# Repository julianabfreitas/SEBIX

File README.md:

# SEBIX
Projeto desenvolvido pela Diretoria 2020 da ADA - Projetos em Engenharia de Computação.
### Membros:
- Érika Cardoso
- Gabriela Vidal
- Juliana Freitas
- Patrick Feitosa

## Descrição do Projeto
Replicação do jogo "Dinosaur Game" feito pelo Google em Arduino. 

## Esquemático
Abaixo encontra-se o esquemático do projeto, utilizando um Arduino Nano.

## Descrição do jogo
Foram utilizados três push buttons que tem as funções de fazer o dinossauro subir na tela, descer na tela e resetar o jogo.
Também são emitidos alertas sonoros pelo buzzer, o potenciômetro foi utilizado para regular o volume do som emitido.

## Componentes utilizados
Para o projeto, utilizamos somente os componentes listados abaixo:
- 1 Arduino Nano
  - Eagle: componente baixado da internet, juntamente com seu modelo 3D
- 1 Leitor LCD 16x2
  - Eagle: componente baixado da internet, juntamente com seu modelo 3D
- 3 Botões
  - Eagle: B3F-40XX (Version 2)
- 1 Potenciômetro
  -  Eagle: 3RP/1610N (Version 2)
- 1 Buzzer
  - Eagle: F/QMB (Version 2)
- 4 Resistores de 10kΩ
  - Eagle: R-US_0207/10 (R-US_) (Version 1)
  
## PCB
Cada um dos integrantes do grupo desenvolveu uma PCB no software Eagle com o objetivo de que todos obtivessem conhecimentos nessa tecnologia. Aqui estão os modelos criados:

## Caixa
A caixa foi desenvolvida no software Fusion360, abaixo estão os modelos desenvolvidos.

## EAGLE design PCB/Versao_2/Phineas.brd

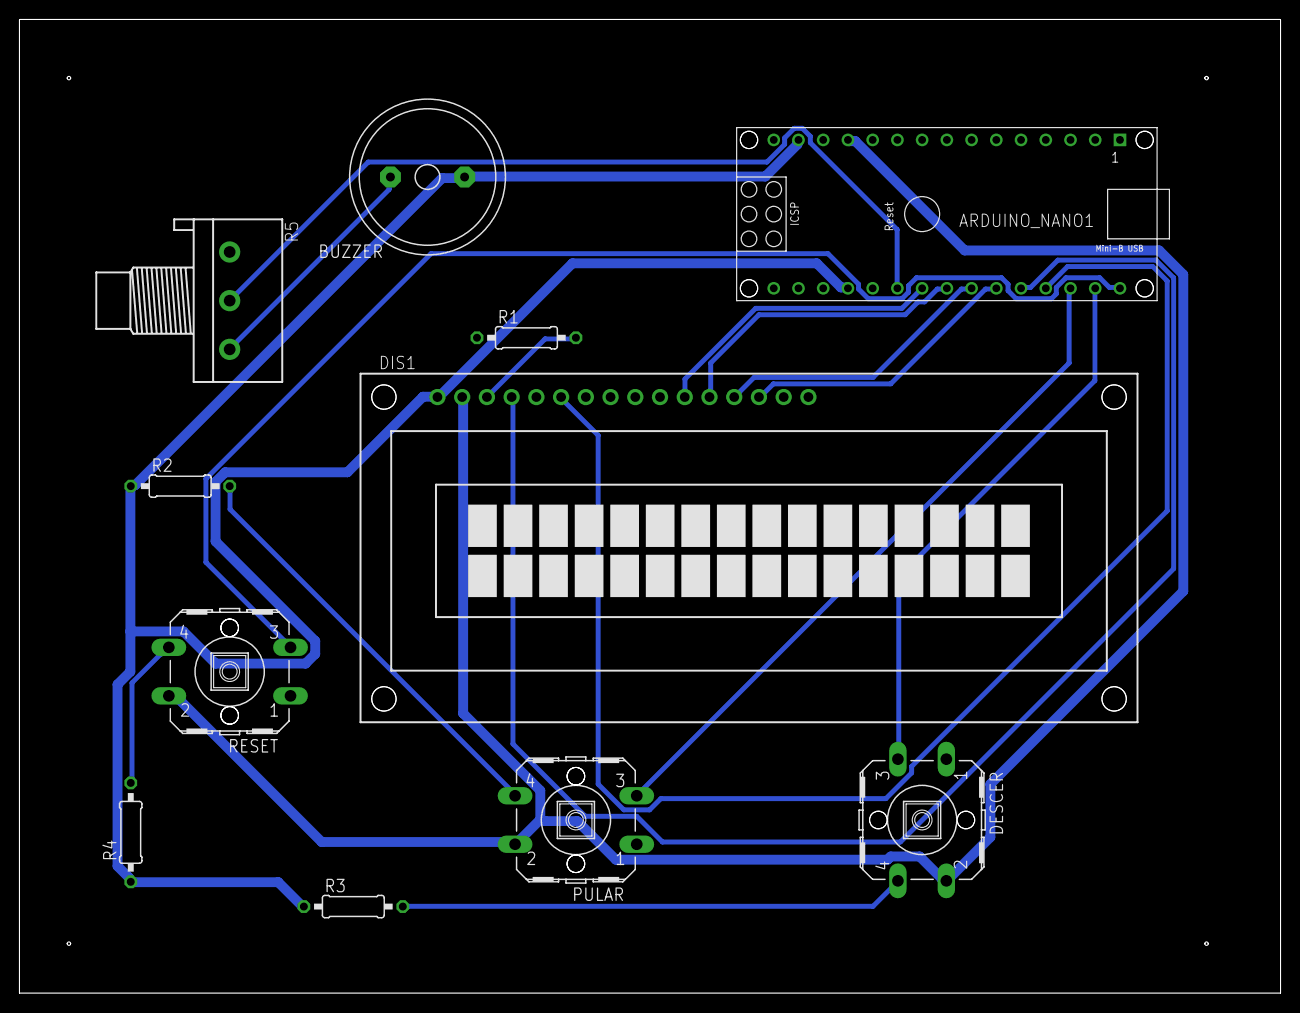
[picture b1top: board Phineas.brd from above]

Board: 2 copper layers, 129.5 x 100.0 mm, 11 parts (0 on the bottom side), 17 nets.

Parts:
ARDUINO_NANO1: ARDUINO_NANO
BUZZER: F/QMB
DESCER: B3F-40XX
DIS1: TUXGR_16X2_R2
PULAR: B3F-40XX
R1, R2, R3, R4: 0207/10
R5: 3RP/1610N
RESET: B3F-40XX

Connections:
GND: ARDUINO_NANO1.14, ARDUINO_NANO1.19, BUZZER.-, DIS1.1, R2.1, R3.1, R4.1
unnamed: DIS1.3, R1.2
unnamed: PULAR.4, R2.2
unnamed: DESCER.4, R3.2
unnamed: ARDUINO_NANO1.26, DIS1.4
unnamed: ARDUINO_NANO1.30, RESET.3
unnamed: ARDUINO_NANO1.29, DESCER.3
unnamed: ARDUINO_NANO1.28, PULAR.3
unnamed: ARDUINO_NANO1.27, DIS1.6
unnamed: BUZZER.+, R5.3
unnamed: ARDUINO_NANO1.25, DIS1.14
unnamed: ARDUINO_NANO1.24, DIS1.13
unnamed: ARDUINO_NANO1.23, DIS1.12
unnamed: ARDUINO_NANO1.22, DIS1.11
unnamed: R4.2, RESET.4
unnamed: ARDUINO_NANO1.21, R5.2
VCC: ARDUINO_NANO1.12, DESCER.2, DIS1.2, PULAR.2, RESET.2

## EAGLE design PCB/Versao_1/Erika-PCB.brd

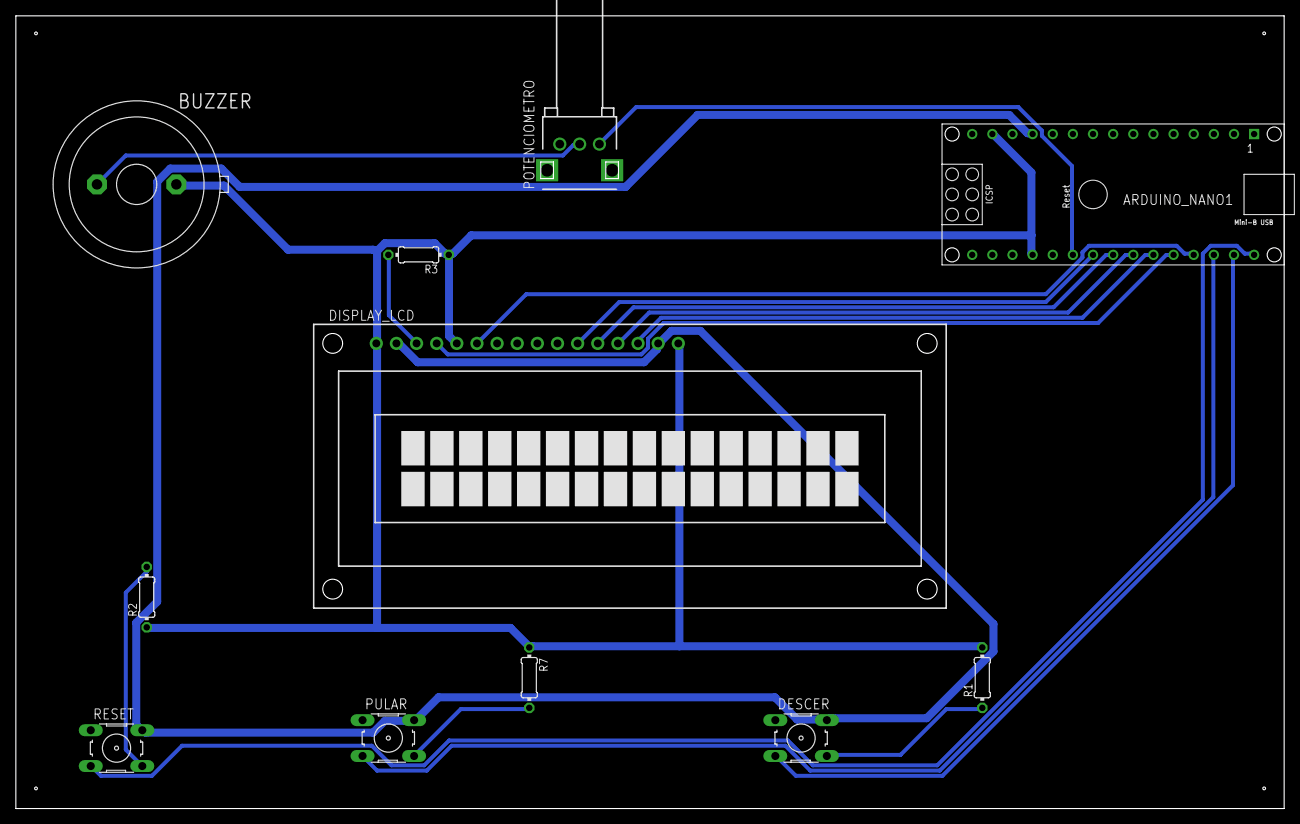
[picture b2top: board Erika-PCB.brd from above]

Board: 2 copper layers, 160.0 x 100.0 mm, 11 parts (0 on the bottom side), 17 nets.

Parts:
ARDUINO_NANO1: ARDUINO_NANO
BUZZER: F/EE21P
DESCER: B3F-10XX
DISPLAY_LCD: TUXGR_16X2_R2
POTENCIOMETRO: EVUE2A; EVUE
PULAR: B3F-10XX
R1, R2, R3, R7: 0204/7
RESET: B3F-10XX

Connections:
GND: ARDUINO_NANO1.14, ARDUINO_NANO1.19, BUZZER.2, DISPLAY_LCD.1, DISPLAY_LCD.5, DISPLAY_LCD.16, R1.2, R2.1, R3.1, R7.1
unnamed: ARDUINO_NANO1.22, DISPLAY_LCD.11
unnamed: DESCER.4, R1.1
unnamed: ARDUINO_NANO1.28, PULAR.3
unnamed: ARDUINO_NANO1.29, DESCER.3
unnamed: ARDUINO_NANO1.30, RESET.3
unnamed: BUZZER.1, POTENCIOMETRO.2
unnamed: ARDUINO_NANO1.23, DISPLAY_LCD.12
unnamed: R2.2, RESET.4
unnamed: PULAR.4, R7.2
unnamed: DISPLAY_LCD.3, R3.2
unnamed: ARDUINO_NANO1.24, DISPLAY_LCD.13
unnamed: ARDUINO_NANO1.25, DISPLAY_LCD.14
unnamed: ARDUINO_NANO1.26, DISPLAY_LCD.4
unnamed: ARDUINO_NANO1.27, DISPLAY_LCD.6
unnamed: ARDUINO_NANO1.21, POTENCIOMETRO.1
VCC: ARDUINO_NANO1.12, DESCER.2, DISPLAY_LCD.2, DISPLAY_LCD.15, PULAR.2, RESET.2

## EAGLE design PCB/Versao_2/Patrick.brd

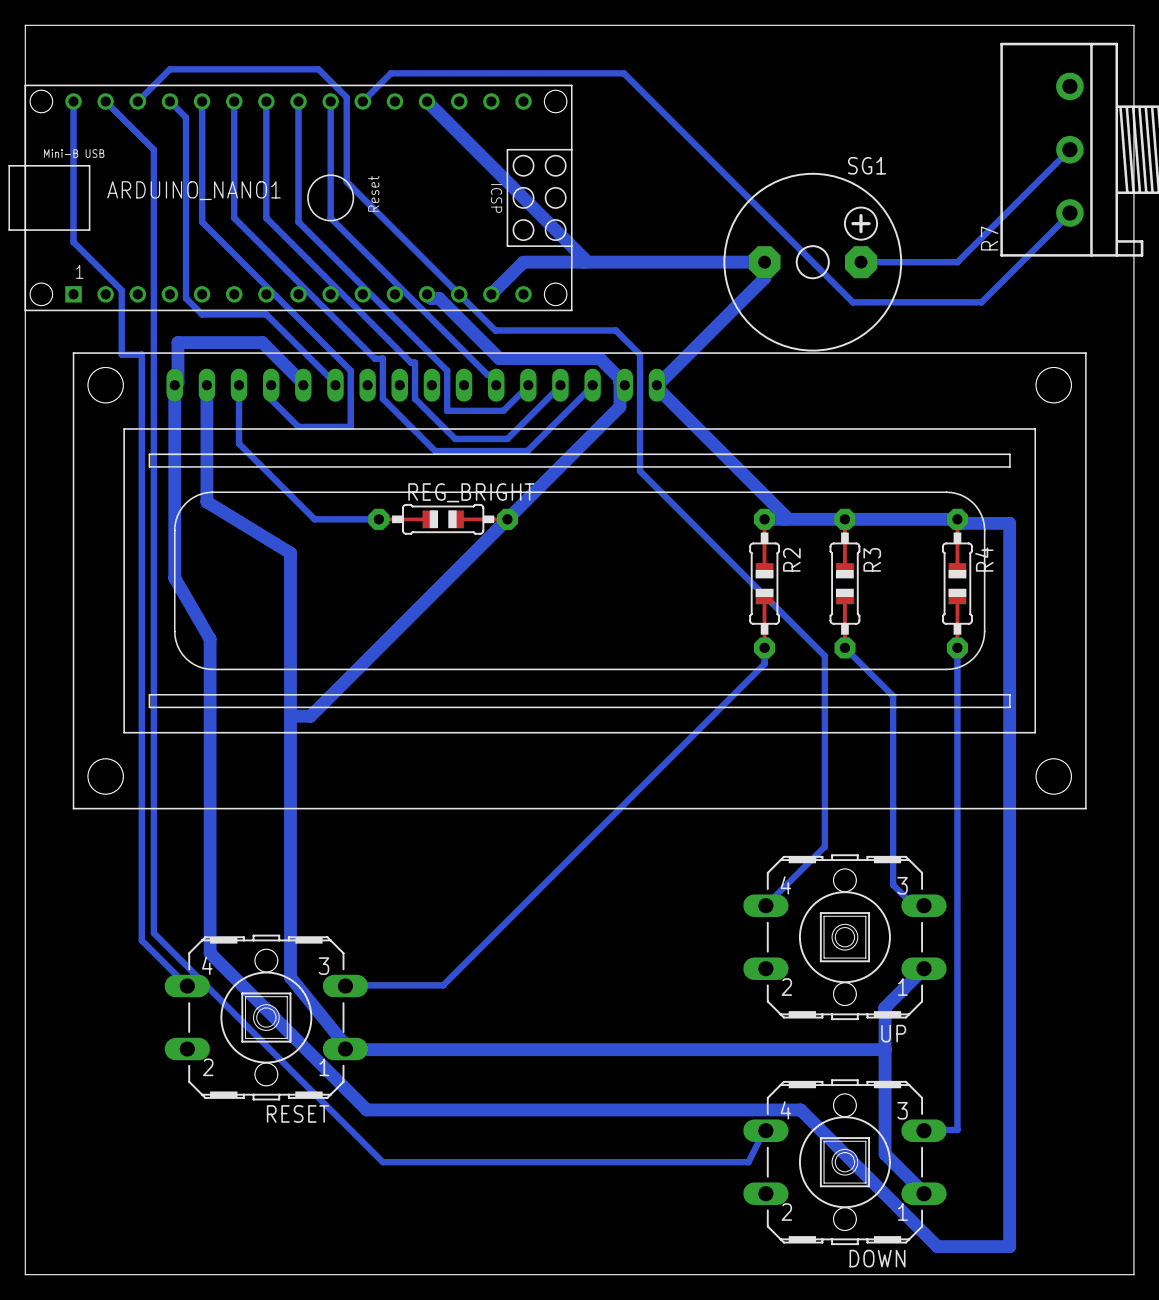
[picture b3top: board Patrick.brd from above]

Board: 2 copper layers, 87.6 x 98.7 mm, 11 parts (0 on the bottom side), 17 nets.

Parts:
ARDUINO_NANO1: ARDUINO_NANO
DOWN: B3F-40XX
R2, R3, R4: 0805-THM
R7: 3RP/1610N
REG_BRIGHT: 0805-THM
RESET: B3F-40XX
SG1: F/CM12P
UP: B3F-40XX
X1: HD44780LCD-1602; LCD1602

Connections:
GND: ARDUINO_NANO1.14, ARDUINO_NANO1.19, R2.1, R3.1, R4.1, SG1.-, X1.1, X1.5, X1.16
unnamed: REG_BRIGHT.1, X1.3
unnamed: ARDUINO_NANO1.28, UP.4
unnamed: ARDUINO_NANO1.29, DOWN.4
unnamed: R3.2, UP.3
unnamed: DOWN.3, R4.2
unnamed: R2.2, RESET.3
unnamed: ARDUINO_NANO1.30, RESET.4
unnamed: ARDUINO_NANO1.27, X1.6
unnamed: ARDUINO_NANO1.26, X1.4
unnamed: ARDUINO_NANO1.25, X1.14
unnamed: ARDUINO_NANO1.24, X1.13
unnamed: ARDUINO_NANO1.23, X1.12
unnamed: ARDUINO_NANO1.22, X1.11
unnamed: ARDUINO_NANO1.21, R7.1
unnamed: R7.2, SG1.+
VCC: ARDUINO_NANO1.12, DOWN.1, REG_BRIGHT.2, RESET.1, UP.1, X1.2, X1.15

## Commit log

2020-01-29 Criação do cenário + Personagens
2020-01-29 Esquemático do Arduino Uno
2020-01-30 Desenho dos personagens
2020-01-30 Código com cenário acelerando
2020-01-31 Parte inicial do código comentada
2020-01-31 Comentando o código
2020-01-31 Adicionando imagem do esquemático
2020-01-31 nomes pasta
2020-01-31 Adicionando structs
2020-01-31 Movimento completo do cenário com aleatoriedade
2020-01-31 Atualizando desenhos
2020-02-04 Pulo (com alguns bugs) e descida do dino implementados. Colisão implementada (com alguns bugs). Botão de reset implementado.
2020-02-04 Esquemático do Arduino Uno com os botões
2020-02-04 README com o esquemático atualizado
2020-02-07 Bugs de dino voador e do reset e o bug do dino que morria do nada
2020-02-07 Esquemático com buzzer
2020-02-07 Adição do score, do buzzer e menu inicial
2020-02-07 código com Arduino Nano e esquemático do Arduino Nano
2020-02-08 README atualizado com a imagem d esquemático do Arduino Nano
2020-05-27 Pasta com esquemáticos de cada membro
2020-06-13 Esquemático da Phineas
2020-06-13 Adicionando esquemático da Érika, o MELHOR
2020-06-13 Reorganização das pastas
2020-06-13 Editando o esquemático phineas
2020-06-13 Editando Esquemático Eagle Band
2020-06-13 Readme com imagem ajustada
2020-06-13 PCB da Band add
2020-06-14 Correção do esquemático
2020-06-14 Adicionando PCB
2020-06-15 PCB arrumada, tamanho 9x11 cm
2020-06-18 Ajeitando nome das pastas código
2020-06-18 Alterando Esquemático Phineas
2020-06-18 Adicionando PCB Phineas
2020-06-18 Arrumando nome pastas código nano
2020-06-20 PCB feita, com rotas ligadas, 9x10cm
2020-06-27 Atualizacao do esquematico e da PCB
2020-06-27 PCB Phineas
2020-06-27 Atualizando a PCB
2020-07-21 Pasta com os componentes 3D
2020-07-21 componentes add
2020-07-21 aaaaa
2020-07-21 Commitando nova versão da PCB
2020-07-22 Esquemático atualizado com os componentes 3D
2020-07-23 PCB Band atualizada com os componentes certos
2020-07-25 logo para a caixa 3D
2020-07-27 Incluindo Versão 2 da PCB, se Deus quiser agora tá certo #fé
2020-07-27 placa patrick atualizada
2020-07-27 Ajustes no modelo exportado para o Fusion
2020-07-27 Ajeitando esquemático Phineas
2020-07-27 Adicionando versão 2 PCB Phineas
2020-07-27 Adicionando componentes 3D
2020-07-27 phineas pcb versao2 pronta
2020-07-28 Ajuste de posicionamento dos componentes na PCB
2020-08-10 Alterando esquemático e board Phineas
2020-08-10 aterações finais board Phineas AMEM
2021-06-07 Imagens da pcb e da caixa foram adicionadas
2021-06-07 Imagem pcb phineas adicionada
2021-06-07 Alguns ajustes
2021-06-07 Ajustes
